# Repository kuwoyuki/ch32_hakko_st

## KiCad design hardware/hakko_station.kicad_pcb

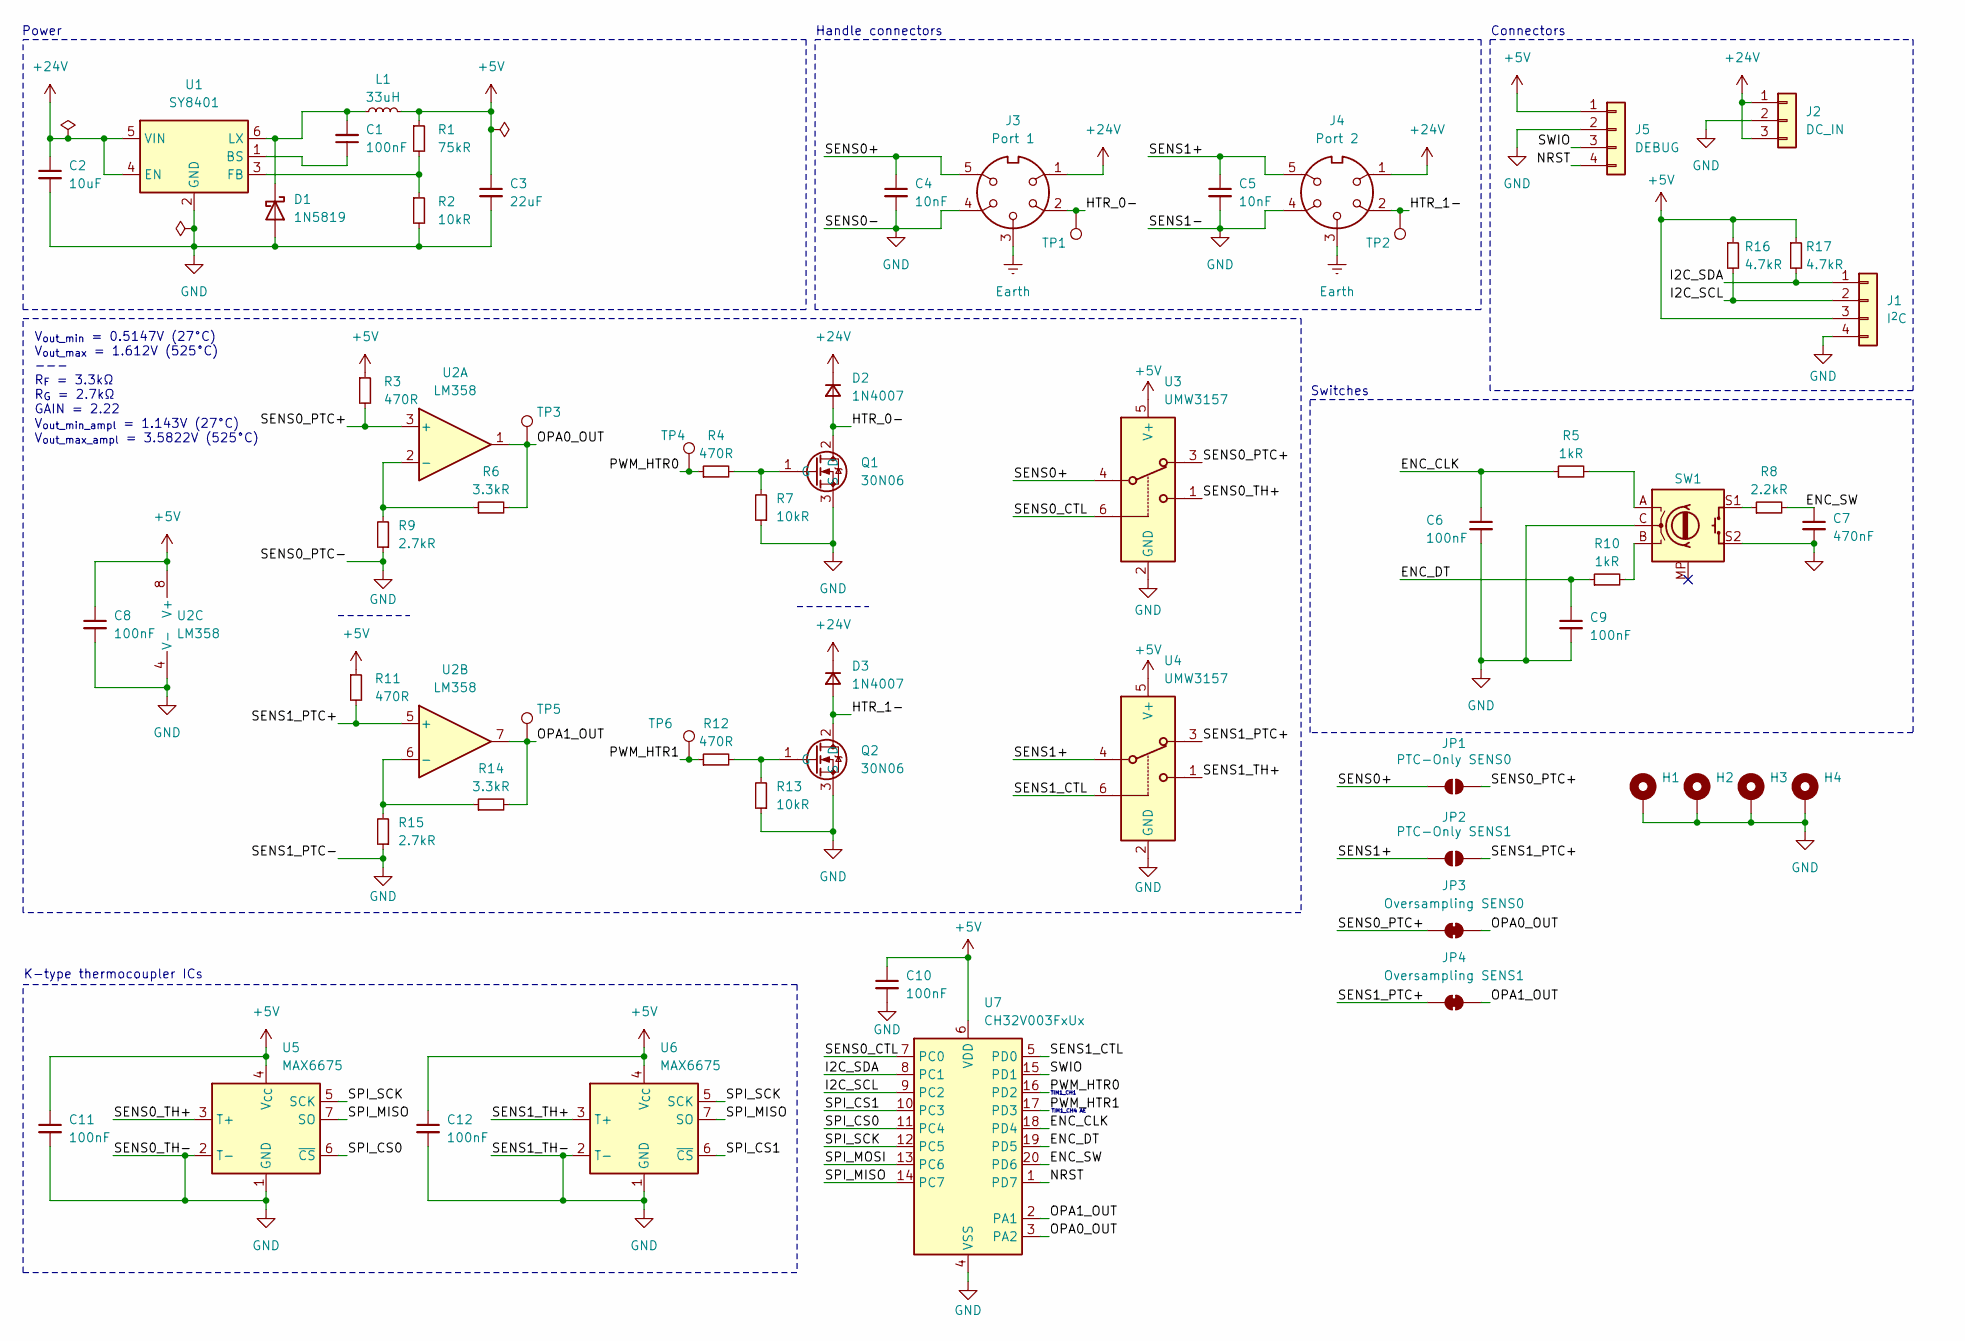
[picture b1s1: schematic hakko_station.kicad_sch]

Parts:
C1, C6, C8, C9, C10, C11, C12: 100nF; C_0402_1005Metric
C2: 10uF; C_1210_3225Metric
C3: 22uF; C_0805_2012Metric
C4, C5: 10nF; C_0402_1005Metric
C7: 470nF; C_0603_1608Metric
D1: 1N5819; D_SOD-123
D2, D3: 1N4007; D_SMA
H1, H2, H3, H4: MountingHole_Pad; MountingHole_3.2mm_M3_DIN965_Pad
J1: I^{2}C; JST_XH_S4B-XH-A_1x04_P2.50mm_Horizontal
J2: DC_IN; SolderWire-0.75sqmm_1x03_P7mm_D1.25mm_OD3.5mm
J3: Port 1; SolderWire-0.5sqmm_1x05_P4.8mm_D0.9mm_OD2.3mm
J4: Port 2; SolderWire-0.5sqmm_1x05_P4.8mm_D0.9mm_OD2.3mm
J5: DEBUG; PinHeader_1x04_P2.54mm_Vertical
JP1: PTC-Only SENS0; SolderJumper-2_P1.3mm_Open_RoundedPad1.0x1.5mm
JP2: PTC-Only SENS1; SolderJumper-2_P1.3mm_Open_RoundedPad1.0x1.5mm
JP3: Oversampling SENS0; SolderJumper-2_P1.3mm_Bridged_RoundedPad1.0x1.5mm
JP4: Oversampling SENS1; SolderJumper-2_P1.3mm_Bridged_RoundedPad1.0x1.5mm
L1: 33uH; L_7.3x7.3_H3.5
Q1, Q2: 30N06; TO-252-2
R1: 75kR; R_0402_1005Metric
R2, R7, R13: 10kR; R_0402_1005Metric
R3, R4, R11, R12: 470R; R_0603_1608Metric
R5, R10: 1kR; R_0402_1005Metric
R6, R14: 3.3kR; R_0603_1608Metric
R8: 2.2kR; R_0402_1005Metric
R9, R15: 2.7kR; R_0402_1005Metric
R16, R17: 4.7kR; R_0402_1005Metric
SW1: RotaryEncoder_Switch_MP; RotaryEncoder_Alps_EC11E-Switch_Vertical_H20mm
TP1, TP2, TP4, TP6: TestPoint; TestPoint_Keystone_5000-5004_Miniature
TP3, TP5: TestPoint; TestPoint_Pad_D1.0mm
U1: SY8401; SOT-23-6
U2: LM358; SOIC-8_3.9x4.9mm_P1.27mm
U3, U4: UMW3157; SOT-363_SC-70-6
U5, U6: MAX6675; SOIC-8_3.9x4.9mm_P1.27mm
U7: CH32V003FxUx; QFN-20-1EP_3x3mm_P0.4mm_EP1.65x1.65mm

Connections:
+5V: C3.1, C8.1, C10.1, C11.1, C12.1, J1.3, J5.1, L1.2, R1.1, R3.1, R11.1, R16.1, R17.1, U2.8 (V+), U3.5 (V+), U4.5 (V+), U5.4 (V_{CC}), U6.4 (V_{CC}), U7.6 (VDD)
+24V: C2.1, D2.1 (K), D3.1 (K), J2.1, J2.3, J3.1, J4.1, U1.4 (EN), U1.5 (VIN)
/ENC_CLK: C6.1, R5.1, U7.18 (PD4)
/ENC_DT: C9.1, R10.1, U7.19 (PD5)
/ENC_SW: C7.1, R8.2, U7.20 (PD6)
/HTR_0-: D2.2 (A), J3.2, Q1.2 (D), TP1.1
/HTR_1-: D3.2 (A), J4.2, Q2.2 (D), TP2.1
/I2C_SCL: J1.2, R16.2, U7.9 (PC2)
/I2C_SDA: J1.1, R17.2, U7.8 (PC1)
/NRST: J5.4, U7.1 (PD7)
/OPA0_OUT: JP3.2 (B), R6.2, TP3.1, U2.1, U7.3 (PA2)
/OPA1_OUT: JP4.2 (B), R14.2, TP5.1, U2.7, U7.2 (PA1)
/PWM_HTR0: R4.1, TP4.1, U7.16 (PD2)
/PWM_HTR1: R12.1, TP6.1, U7.17 (PD3)
/SENS0+: C4.1, J3.5, JP1.1 (A), U3.4
/SENS0_CTL: U3.6, U7.7 (PC0)
/SENS0_PTC+: JP1.2 (B), JP3.1 (A), R3.2, U2.3 (+), U3.3
/SENS0_TH+: U3.1, U5.3 (T+)
/SENS1+: C5.1, J4.5, JP2.1 (A), U4.4
/SENS1_CTL: U4.6, U7.5 (PD0)
/SENS1_PTC+: JP2.2 (B), JP4.1 (A), R11.2, U2.5 (+), U4.3
/SENS1_TH+: U4.1, U6.3 (T+)
/SPI_CS0: U5.6 (~CS), U7.11 (PC4)
/SPI_CS1: U6.6 (~CS), U7.10 (PC3)
/SPI_MISO: U5.7 (SO), U6.7 (SO), U7.14 (PC7)
/SPI_MOSI: U7.13 (PC6)
/SPI_SCK: U5.5 (SCK), U6.5 (SCK), U7.12 (PC5)
/SWIO: J5.3, U7.15 (PD1)
Earth: J3.3, J4.3
GND: C2.2, C3.2, C4.2, C5.2, C6.2, C7.2, C8.2, C9.2, C10.2, C11.2, C12.2, D1.2 (A), H1.1, H2.1, H3.1, H4.1, J1.4, J2.2, J3.4, J4.4, J5.2, Q1.3 (S), Q2.3 (S), R2.2, R7.1, R9.1, R13.1, R15.1, SW1.C, SW1.S2, U1.2 (GND), U2.4 (V-), U3.2 (GND), U4.2 (GND), U5.1 (GND), U5.2 (T-), U6.1 (GND), U6.2 (T-), U7.4 (VSS), U7.21 (VSS)
unnamed: C1.2, D1.1 (K), L1.1, U1.6 (LX)
unnamed: Q1.1 (G), R4.2, R7.2
unnamed: Q2.1 (G), R12.2, R13.2
unnamed: R5.2, SW1.A
unnamed: R8.1, SW1.S1
unnamed: R10.2, SW1.B
unnamed: C1.1, U1.1 (BS)
unnamed: R1.2, R2.1, U1.3 (FB)
unnamed: R6.1, R9.2, U2.2 (-)
unnamed: R14.1, R15.2, U2.6 (-)

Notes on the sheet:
V_{out_min} = 0.5147V (27°C) V_{out_max} = 1.612V (525°C) --- R_{F} = 3.3kΩ R_{G} = 2.7kΩ GAIN = 2.22 V_{out_min_ampl} = 1.143V (27°C) V_{out_max_ampl} = 3.5822V (525°C)
Handle connectors
Power
Switches
K-type thermocoupler ICs
TIM1_CH1
Connectors
TIM1_CH4 AE

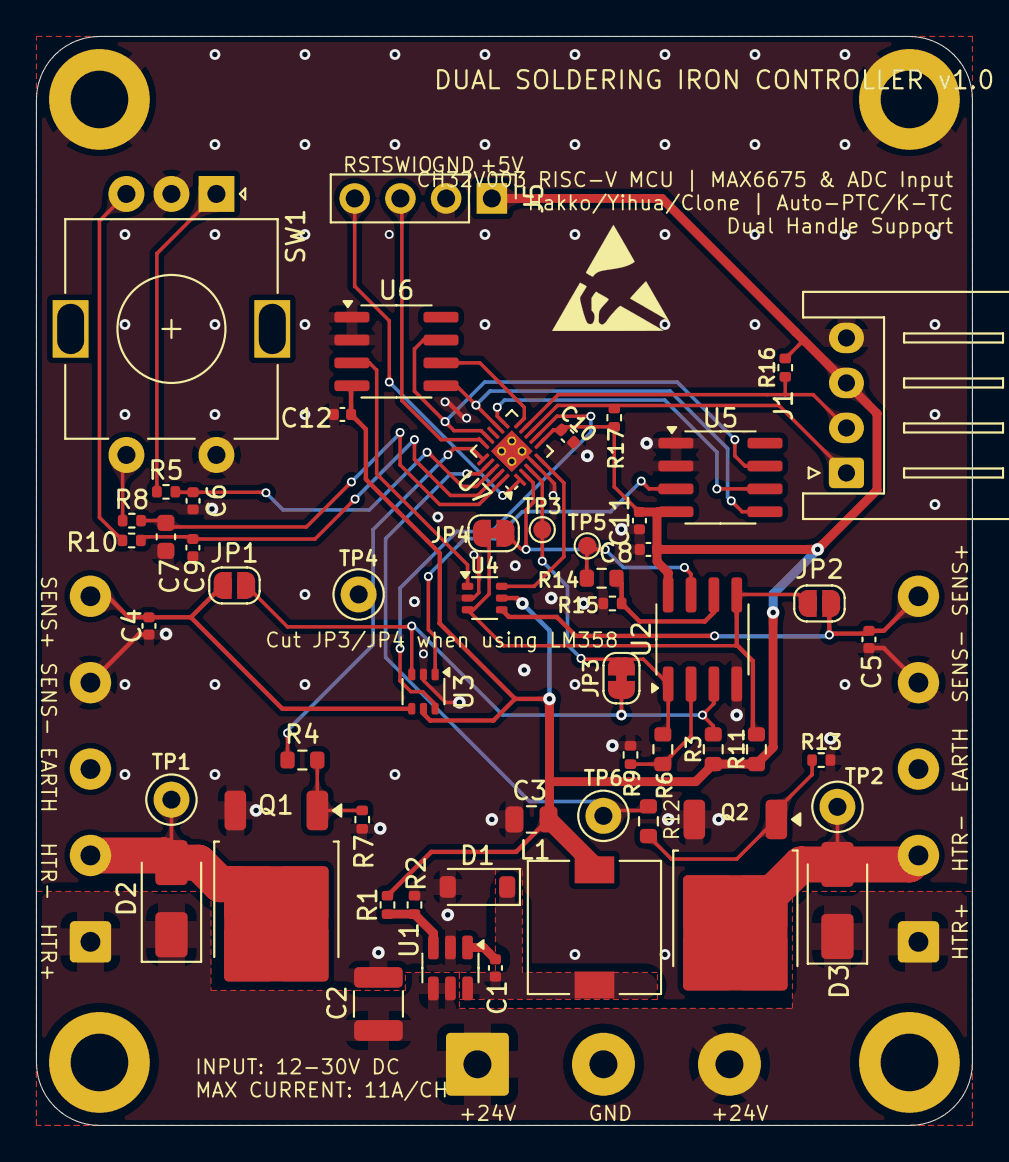
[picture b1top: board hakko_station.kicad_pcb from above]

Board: 2 copper layers, 52.0 x 60.5 mm, 62 parts (0 on the bottom side), 39 nets.

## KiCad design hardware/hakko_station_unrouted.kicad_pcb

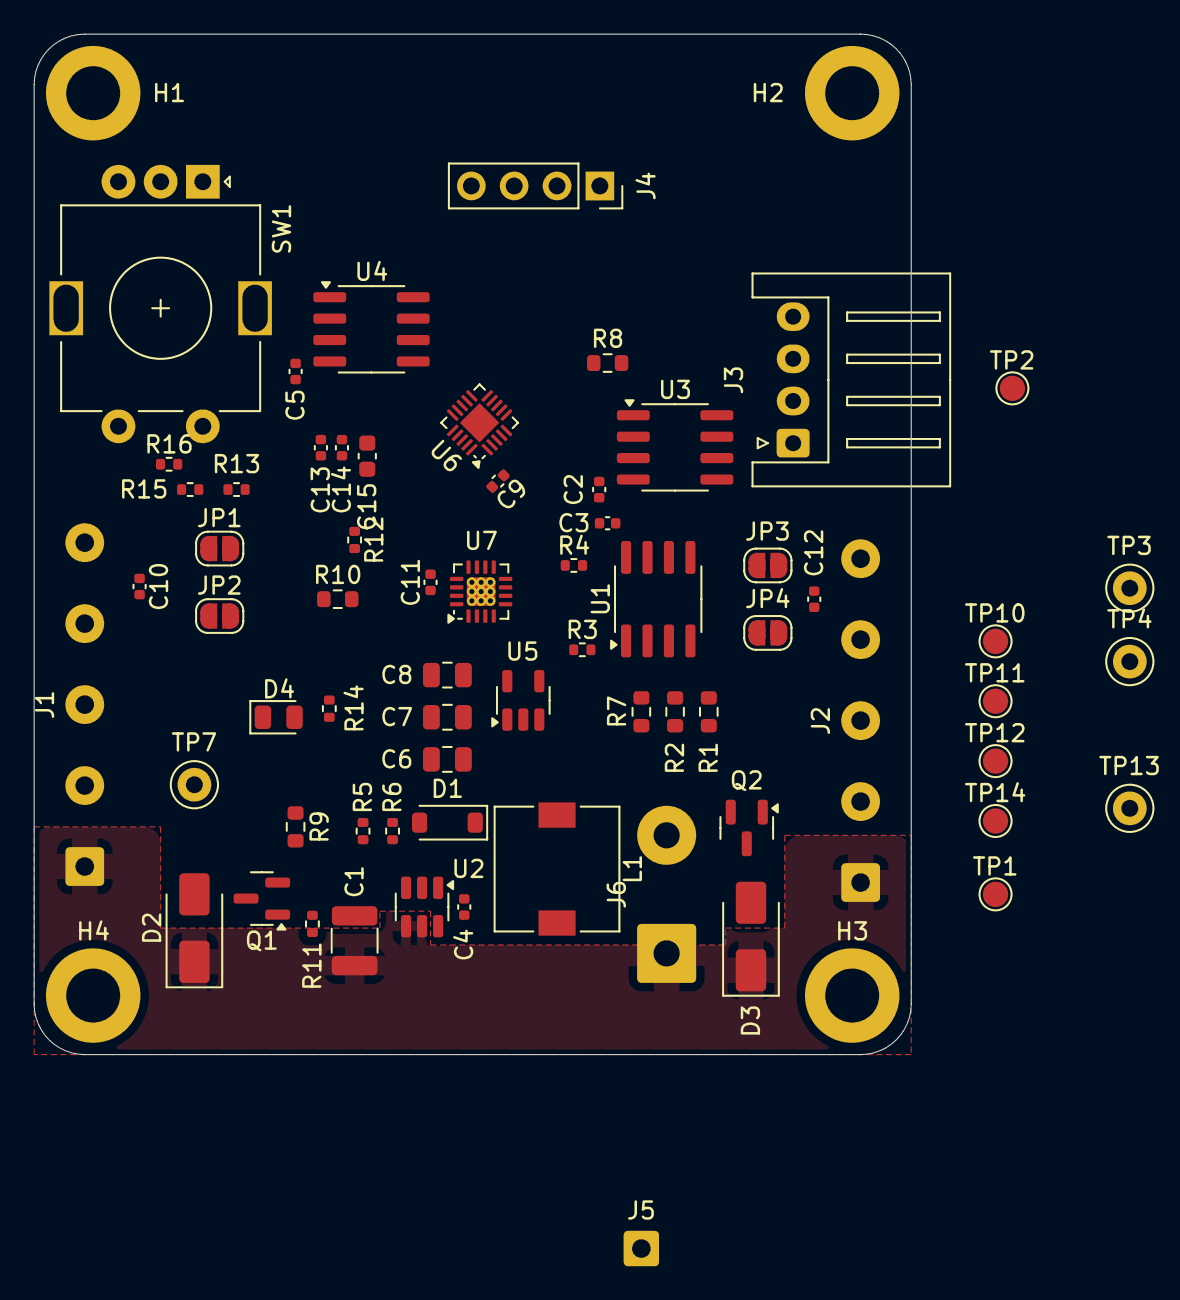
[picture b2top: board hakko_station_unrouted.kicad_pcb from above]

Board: 4 copper layers, 52.0 x 60.5 mm, 70 parts (0 on the bottom side), 45 nets, no tracks yet.

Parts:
C1: 10uF; C_1210_3225Metric
C2, C3, C4, C5, C9, C11, C13, C14: 100nF; C_0402_1005Metric
C6: 22uF; C_0805_2012Metric
C7, C8: 1uF; C_0805_2012Metric
C10, C12: 10nF; C_0402_1005Metric
C15: 470nF; C_0603_1608Metric
D1: 1N5819; D_SOD-123
D2, D3: 1N4007; D_SMA
D4: PWR; LED_0805_2012Metric
H1, H2, H3, H4: MountingHole_Pad; MountingHole_3.2mm_M3_DIN965_Pad
J1: Port 1; SolderWire-0.5sqmm_1x05_P4.8mm_D0.9mm_OD2.3mm
J2: Port 2; SolderWire-0.5sqmm_1x05_P4.8mm_D0.9mm_OD2.3mm
J3: I^{2}C; JST_XH_S4B-XH-A_1x04_P2.50mm_Horizontal
J4: DEBUG; PinSocket_1x04_P2.54mm_Vertical
J5: ESD; SolderWire-0.5sqmm_1x01_D0.9mm_OD2.1mm
J6: DC_IN; SolderWire-0.75sqmm_1x02_P7mm_D1.25mm_OD3.5mm
JP1, JP2, JP3, JP4: SolderJumper_2_Open; SolderJumper-2_P1.3mm_Open_RoundedPad1.0x1.5mm
L1: 33uH; L_7.3x7.3_H3.5
Q1, Q2: AO3400A; SOT-23
R1, R2: 180R; R_0603_1608Metric
R3, R4, R6, R11, R12: 10kR; R_0402_1005Metric
R5: 75kR; R_0402_1005Metric
R7, R8: 6.8kR; R_0603_1608Metric
R9, R10: 47R; R_0603_1608Metric
R13, R14, R15: 1kR; R_0402_1005Metric
R16: 2.2kR; R_0402_1005Metric
SW1: RotaryEncoder_Switch_MP; RotaryEncoder_Alps_EC11E-Switch_Vertical_H20mm
TP1, TP2, TP10, TP11, TP12, TP14: TestPoint; TestPoint_Pad_D1.5mm
TP3, TP4, TP7, TP13: TestPoint; TestPoint_Keystone_5000-5004_Miniature
U1: LM358; SOIC-8_3.9x4.9mm_P1.27mm
U2: SY8401; SOT-23-6
U3, U4: MAX31855KASA; SOIC-8_3.9x4.9mm_P1.27mm
U5: RT9013; SOT-23-5
U6: CH32V003FxUx; QFN-20-1EP_3x3mm_P0.4mm_EP1.65x1.65mm
U7: RS2299; QFN-16-1EP_3x3mm_P0.5mm_EP1.7x1.7mm_ThermalVias

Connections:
+3V3: C2.1, C3.1, C5.1, C8.1, C9.1, C11.1, J3.3, J4.1, R1.1, R2.1, R14.1, U1.8 (V+), U3.4 (V_{CC}), U4.4 (V_{CC}), U5.5 (VOUT), U6.6 (VDD), U7.14 (VDD)
+5V: C6.1, C7.1, L1.2, R5.1, U5.1 (VIN), U5.3 (EN)
+24V: C1.1, D2.1 (K), D3.1 (K), J1.1, J2.1, J6.1, U2.4 (EN), U2.5 (VIN)
/ENC_CLK: C13.1, R13.1, U6.18 (PD4)
/ENC_DT: C14.1, R15.1, U6.19 (PD5)
/ENC_SW: C15.1, R16.2, U6.20 (PD6)
/HTR_0-: D2.2 (A), J1.2, Q1.3 (D), TP7.1
/HTR_1-: D3.2 (A), J2.2, Q2.3 (D), TP13.1
/I2C_SCL: J3.2, U6.9 (PC2)
/I2C_SDA: J3.1, U6.8 (PC1)
/NRST: J4.4, U6.1 (PD7)
/OPA0_OUT: R7.2, TP1.1, U1.1, U6.3 (PA2)
/OPA1_OUT: R8.2, TP2.1, U1.7, U6.2 (PA1)
/PWM_HTR0: R9.1, TP3.1, U6.16 (PD2)
/PWM_HTR1: R10.1, TP4.1, U6.17 (PD3)
/SENS0+: C10.1, J1.5, JP1.1 (A), U7.16 (COM1)
/SENS0-: C10.2, J1.4, JP2.1 (A), U7.4 (COM2)
/SENS0_CTL: U6.7 (PC0), U7.2 (IN1-2)
/SENS0_PTC+: JP1.2 (B), R2.2, U1.3 (+), U7.1 (NC1)
/SENS0_TH+: U3.3 (T+), U7.15 (NO1)
/SENS0_TH-: U3.2 (T-), U7.3 (NO2)
/SENS1+: C12.1, J2.5, JP3.1 (A), U7.8 (COM3)
/SENS1-: C12.2, J2.4, JP4.1 (A), U7.12 (COM4)
/SENS1_CTL: U6.5 (PD0), U7.10 (IN3-4)
/SENS1_PTC+: JP3.2 (B), R1.2, U1.5 (+), U7.9 (NC3)
/SENS1_TH+: U4.3 (T+), U7.7 (NO3)
/SENS1_TH-: U4.2 (T-), U7.11 (NO4)
/SPI_CS0: TP12.1, U3.6 (~CS), U6.11 (PC4)
/SPI_CS1: TP14.1, U4.6 (~CS), U6.10 (PC3)
/SPI_MISO: TP11.1, U3.7 (SO), U4.7 (SO), U6.14 (PC7)
/SPI_SCK: TP10.1, U3.5 (SCK), U4.5 (SCK), U6.12 (PC5)
/SWIO: J4.3, U6.15 (PD1)
Earth: J1.3, J2.3, J5.1
GND: C1.2, C2.2, C3.2, C5.2, C6.2, C7.2, C8.2, C9.2, C11.2, C13.2, C14.2, C15.2, D1.2 (A), D4.1 (K), H1.1, H2.1, H3.1, H4.1, J3.4, J4.2, J6.2, JP2.2 (B), JP4.2 (B), Q1.2 (S), Q2.2 (S), R3.1, R4.1, R6.2, R11.1, R12.1, SW1.C, SW1.S2, U1.4 (V-), U2.2 (GND), U3.1 (GND), U4.1 (GND), U5.2 (GND), U6.4 (VSS), U6.21 (VSS), U7.5 (NC2), U7.6 (GND), U7.13 (NC4), U7.17 (GND)
unnamed: C4.2, D1.1 (K), L1.1, U2.6 (LX)
unnamed: D4.2 (A), R14.2
unnamed: Q1.1 (G), R9.2, R11.2
unnamed: Q2.1 (G), R10.2, R12.2
unnamed: R13.2, SW1.A
unnamed: R15.2, SW1.B
unnamed: R16.1, SW1.S1
unnamed: R3.2, R7.1, U1.2 (-)
unnamed: R4.2, R8.1, U1.6 (-)
unnamed: C4.1, U2.1 (BS)
unnamed: R5.2, R6.1, U2.3 (FB)

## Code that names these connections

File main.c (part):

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
// io
#define ENC_PORT GPIOD
#define ENC_CLK_PIN PD4
#define ENC_DT_PIN PD5
#define ENC_SW_PIN PD6
#define ENC_CLK_PIN_NUM 4
#define ENC_DT_PIN_NUM 5
#define ENC_SW_PIN_NUM 6

#define PIN_ADC0 PA2
#define PIN_ADC1 PA1

#define PWM_HTR0_PIN PD2
#define PWM_HTR1_PIN PD3

// system parms
#define ADC_MAX 4095
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  }

  // encoder sw press
  bool sw_is_down = (funDigitalRead(ENC_SW_PIN) == 0);
  if (sw_is_down) {
    if (sw_down_time == 0) {
      sw_down_time = current_time;
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  RCC->APB2PCENR |= RCC_APB2Periph_GPIOA | RCC_APB2Periph_ADC1;
  RCC->AHBPCENR |= RCC_AHBPeriph_DMA1;

  funPinMode(PIN_ADC0, GPIO_CFGLR_IN_ANALOG); // PA2 -> ADC_IN0
  funPinMode(PIN_ADC1, GPIO_CFGLR_IN_ANALOG); // PA1 -> ADC_IN1

  RCC->APB2PRSTR |= RCC_APB2Periph_ADC1;
  RCC->APB2PRSTR &= ~RCC_APB2Periph_ADC1;
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  RCC->APB2PCENR |= RCC_APB2Periph_GPIOD | RCC_APB2Periph_TIM1;
  RCC->APB1PCENR |= RCC_APB1Periph_TIM2;

  funPinMode(PWM_HTR0_PIN, GPIO_CFGLR_OUT_10Mhz_AF_PP);
  funPinMode(PWM_HTR1_PIN, GPIO_CFGLR_OUT_10Mhz_AF_PP);

  const uint16_t psc = 1;

  // TIM1 for heater 0 (PD2)
  RCC->APB2PRSTR |= RCC_APB2Periph_TIM1;
  RCC->APB2PRSTR &= ~RCC_APB2Periph_TIM1;
  TIM1->PSC = psc;
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  TIM1->SWEVGR |= TIM1_SWEVGR_UG;
  TIM1->CTLR1 |= TIM1_CTLR1_CEN;

  // TIM2 for heater 1 (PD3)
  TIM2->PSC = psc;
  TIM2->ATRLR = PWM_PERIOD;
  TIM2->CHCTLR1 |= TIM2_CHCTLR1_OC2M_2 | TIM2_CHCTLR1_OC2M_1;
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void encoder_interrupt_init(void) {
  RCC->APB2PCENR |= RCC_APB2Periph_GPIOD | RCC_APB2Periph_AFIO;

  funPinMode(ENC_CLK_PIN, GPIO_CFGLR_IN_PUPD);
  funDigitalWrite(ENC_CLK_PIN, 1);
  funPinMode(ENC_DT_PIN, GPIO_CFGLR_IN_PUPD);
  funDigitalWrite(ENC_DT_PIN, 1);
  funPinMode(ENC_SW_PIN, GPIO_CFGLR_IN_PUPD);
  funDigitalWrite(ENC_SW_PIN, 1);

  AFIO->EXTICR |=
      AFIO_EXTICR_EXTI4_PD | AFIO_EXTICR_EXTI5_PD | AFIO_EXTICR_EXTI6_PD;
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
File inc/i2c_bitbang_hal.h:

#ifndef _I2C_BITBANG_HAL_H
#define _I2C_BITBANG_HAL_H

#ifndef I2C_ADDR_7BIT
#define I2C_ADDR_7BIT 0x3c
#endif

#ifndef I2C_SDA_PIN
#define I2C_SDA_PIN PC1
#endif
#ifndef I2C_SCL_PIN
#define I2C_SCL_PIN PC2
#endif

#define SCL_HIGH() funDigitalWrite(I2C_SCL_PIN, 1)
#define SCL_LOW() funDigitalWrite(I2C_SCL_PIN, 0)
#define SDA_HIGH() funDigitalWrite(I2C_SDA_PIN, 1)
#define SDA_LOW() funDigitalWrite(I2C_SDA_PIN, 0)

static void i2c_hal_setup(void) {
  funGpioInitAll();
  funPinMode(I2C_SDA_PIN, GPIO_CFGLR_OUT_10Mhz_PP);
  funDigitalWrite(I2C_SDA_PIN, 1);
  funPinMode(I2C_SCL_PIN, GPIO_CFGLR_OUT_10Mhz_PP);
  funDigitalWrite(I2C_SCL_PIN, 1);
}

#endif // _I2C_BITBANG_HAL_H

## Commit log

2025-09-16 rm bin
